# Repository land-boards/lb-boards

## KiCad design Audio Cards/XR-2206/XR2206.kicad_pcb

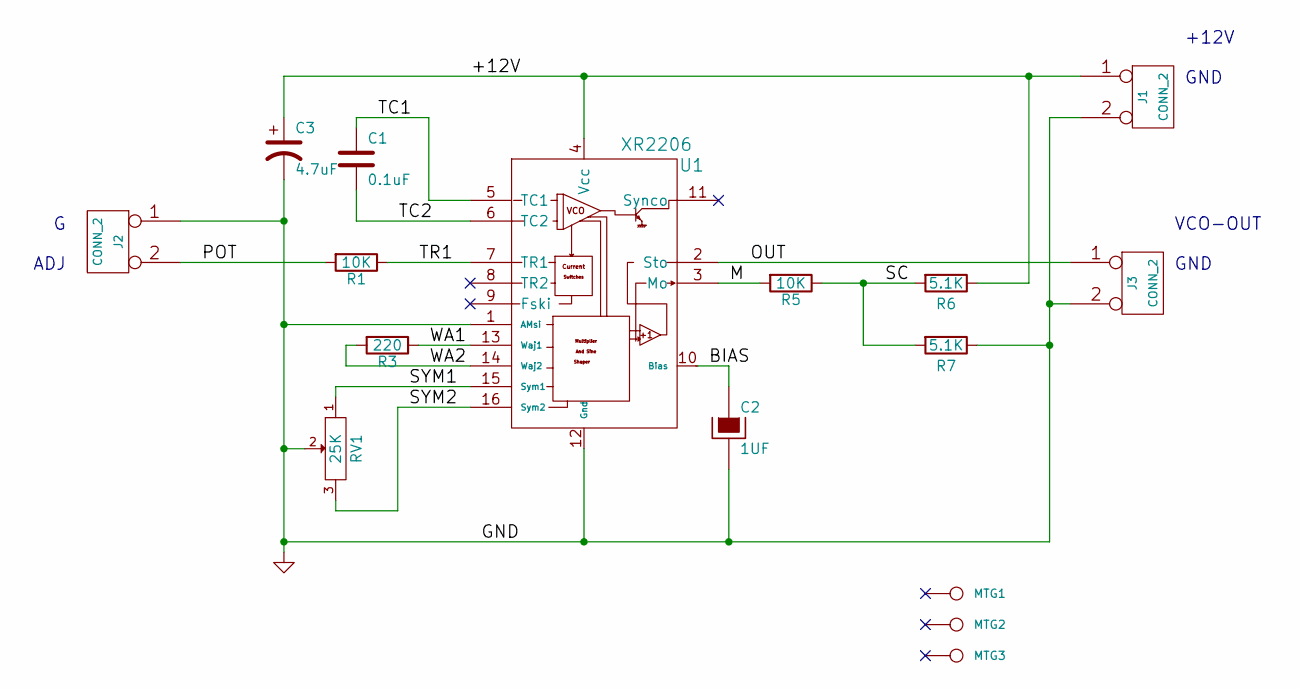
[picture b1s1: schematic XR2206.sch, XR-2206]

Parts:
C1: 0.1uF
C2: 1UF
C3: 4.7uF
J1, J2, J3: CONN_2
MTG1, MTG2, MTG3: CONN_1
R1, R5: 10K
R3: 220
R6, R7: 5.1K
RV1: 25K
U1: XR2206

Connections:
/+12V: C3.1, J1.1, R6.1, U1.4 (Vcc)
/BIAS: C2.1, U1.10 (Bias)
/M: R5.2, U1.3 (Mo)
/OUT: J3.1, U1.2 (Sto)
/POT: J2.2 (PM), R1.2
/SC: R5.1, R6.2, R7.2
/SYM1: RV1.1, U1.15 (Sym1)
/SYM2: RV1.3, U1.16 (Sym2)
/TC1: C1.1, U1.5 (TC1)
/TC2: C1.2, U1.6 (TC2)
/TR1: R1.1, U1.7 (TR1)
/WA1: R3.1, U1.13 (Waj1)
/WA2: R3.2, U1.14 (Waj2)
GND: C2.2, C3.2, J1.2 (PM), J2.1, J3.2 (PM), R7.1, RV1.2, U1.1 (AMsi), U1.12 (Gnd)

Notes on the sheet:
G ADJ
VCO-OUT GND
+12V GND

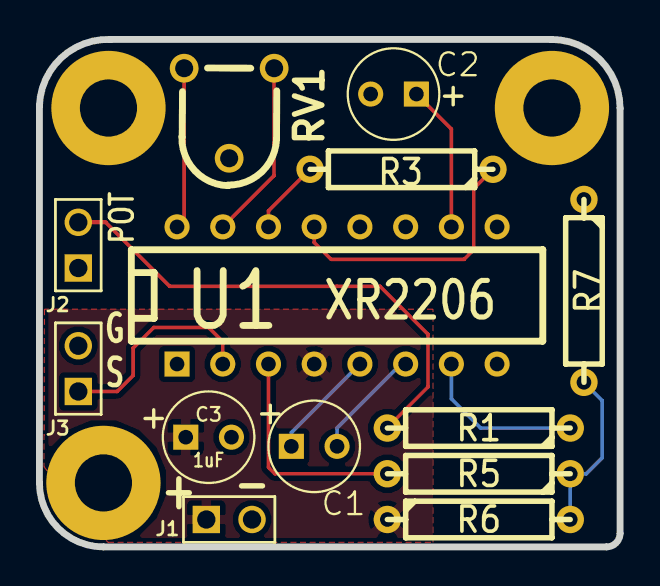
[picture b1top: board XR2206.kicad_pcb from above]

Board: 2 copper layers, 32.3 x 28.2 mm, 16 parts (0 on the bottom side), 14 nets.

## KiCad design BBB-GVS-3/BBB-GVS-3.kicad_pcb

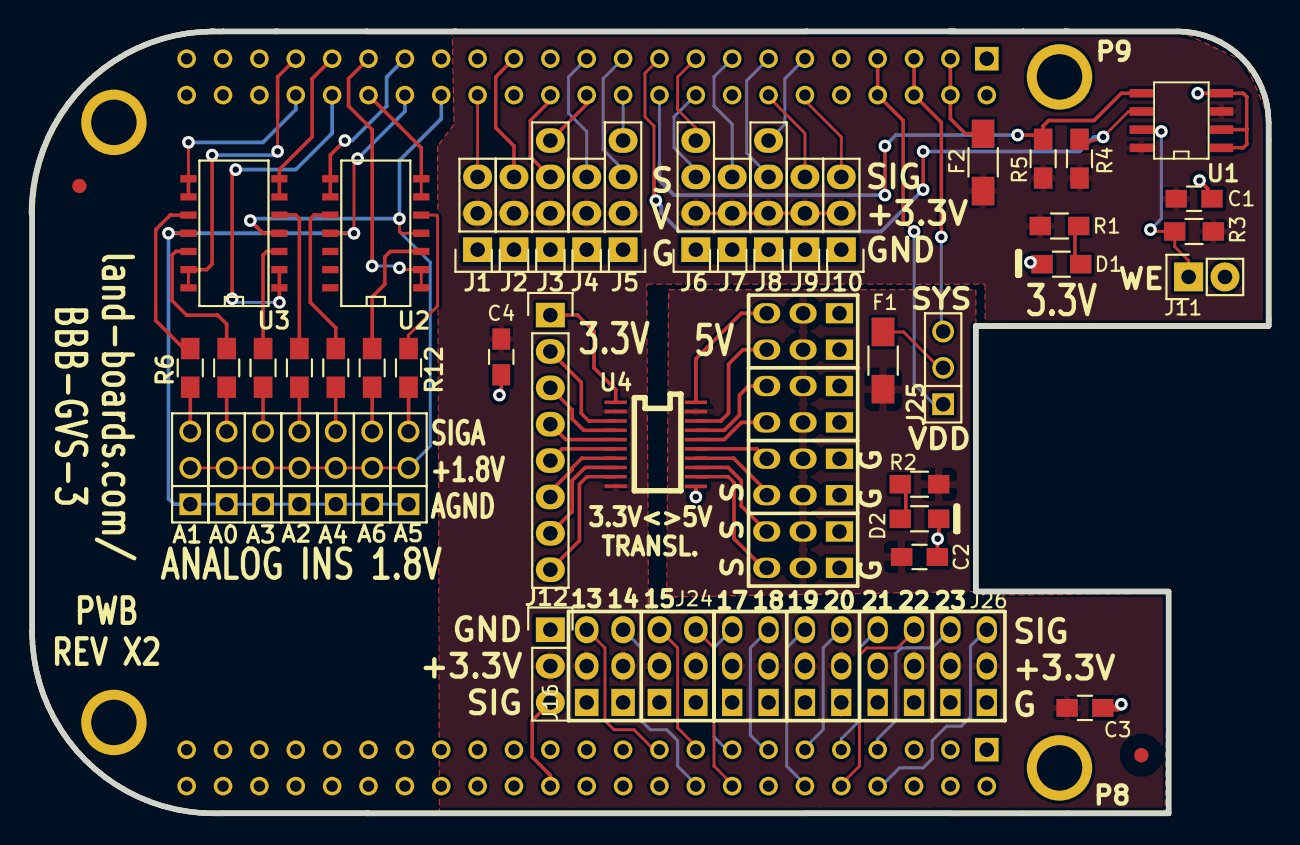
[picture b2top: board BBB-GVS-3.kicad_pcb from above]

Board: 2 copper layers, 86.4 x 54.6 mm, 53 parts (1 on the bottom side), 78 nets.

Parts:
A0, A1, A2, A3, A4, A5, A6: CONN_3; PIN_ARRAY_3X1
BRD1: BEAGLEBONE
C1: 1uF; C_0805_HandSoldering
C2, C3, C4: 104; C_0805_HandSoldering
D1, D2: LED; R_0805_HandSoldering
F1, F2: FUSE; C_1206_HandSoldering
FID1, FID2: CONN_1; FIDUCIAL
J1, J2, J4, J7, J9, J10, J12: CONN_3; Pin_Header_Straight_1x03
J3, J5, J6, J8: CONN_4; Pin_Header_Straight_1x04
J11: CONN_2; Pin_Header_Straight_1x02
J16: GVS-4X3; Pin_Header_Straight_3x04
J24, J26: GVS-8X3; Pin_Header_Straight_3x08
J25: CONN_3; PIN_ARRAY_3X1
P1: CONN_8; Pin_Header_Straight_1x08
R1: 120; R_0805_HandSoldering
R2: 330; R_0805_HandSoldering
R3, R4, R5: 5.6K; R_0805_HandSoldering
R6, R7, R8, R9, R10, R11, R12: 10K; R_0805_HandSoldering
TEST: COUPON; REV_BLOCK
TESTED1: COUPON; REV_BLOCK
U1: I2C-EEPROM; SO8E-wider
U2, U3: MCP6004-I/SL; SOIC-14_N
U4: TXS0108EPWR; SOG20

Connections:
/P8 Connector/EHRPWM2A: BRD1.B19, J16.3
/P8 Connector/EHRPWM2B: BRD1.B13, J24.6
/P8 Connector/GPIO0_27: BRD1.B17, J16.9
/P8 Connector/GPIO1_12: BRD1.B12, J24.9
/P8 Connector/GPIO1_13: BRD1.B11, J24.12
/P8 Connector/GPIO1_14: BRD1.B16, J16.12
/P8 Connector/GPIO1_15: BRD1.B15, J24.3
/P8 Connector/GPIO1_29: BRD1.B26, J12.3
/P8 Connector/GPIO2_1: BRD1.B18, J16.6
/P8 Connector/TIMER4: BRD1.B7, J24.21
/P8 Connector/TIMER5: BRD1.B9, J24.15
/P8 Connector/TIMER6: BRD1.B10, J24.18
/P8 Connector/TIMER7: BRD1.B8, J24.24
/P9 Connector/EHRPWM1A: BRD1.C14, J9.3
/P9 Connector/GPIO1_16: BRD1.C15, J7.3
/P9 Connector/GPIO1_17: BRD1.C23, J4.3
/P9 Connector/GPIO1_28: BRD1.C12, J10.3
/P9 Connector/GPIO3_19: BRD1.C27, J2.3
/P9 Connector/I2C1_SCL: BRD1.C17, J6.4
/P9 Connector/I2C1_SDA: BRD1.C18, J6.3
/P9 Connector/SPI1_D1: BRD1.C30, J1.3
/P9 Connector/UART1_RXD: BRD1.C26, J3.3
/P9 Connector/UART1_TXD: BRD1.C24, J3.4
/P9 Connector/UART2_RXD: BRD1.C22, J5.4
/P9 Connector/UART2_TXD: BRD1.C21, J5.3
/P9 Connector/UART4_RXD: BRD1.C11, J8.4
/P9 Connector/UART4_TXD: BRD1.C13, J8.3
AIN0: BRD1.C39, U3.13, U3.14
AIN1: BRD1.C40, U3.8, U3.9
AIN2: BRD1.C37, U3.6, U3.7
AIN3: BRD1.C38, U3.1, U3.2
AIN4: BRD1.C33, U2.8, U2.9
AIN5: BRD1.C36, U2.6, U2.7
AIN6: BRD1.C35, U2.1, U2.2
GND: BRD1.B1, BRD1.B2, BRD1.C1, BRD1.C2, BRD1.C43, BRD1.C44, BRD1.C45, BRD1.C46, C1.2, C2.2, C3.2, C4.2, D1.2, D2.2, J1.1, J2.1, J3.1, J4.1, J5.1, J6.1, J7.1, J8.1, J9.1, J10.1, J11.2, J12.1, J16.1, J16.4, J16.7, J16.10, J24.1, J24.4, J24.7, J24.10, J24.13, J24.16, J24.19, J24.22, J26.1, J26.4, J26.7, J26.10, J26.13, J26.16, J26.19, J26.22, U1.1, U1.2, U1.4, U4.11
GNDA_ADC: A0.1, A1.1, A2.1, A3.1, A4.1, A5.1, A6.1, BRD1.C34, U2.11, U3.11
I2C2_SCL: BRD1.C19, R4.2, U1.6
I2C2_SDA: BRD1.C20, R5.2, U1.5
unnamed: A0.3, R11.2
unnamed: A1.3, R9.2
unnamed: A2.3, R7.2
unnamed: A3.3, R12.2
unnamed: A4.3, R10.2
unnamed: A5.3, R8.2
unnamed: A6.3, R6.2
unnamed: D1.1, R1.2
unnamed: D2.1, R2.2
unnamed: F1.2, J25.2
unnamed: J11.1, R3.2, U1.7
unnamed: J26.3, U4.12
unnamed: J26.6, U4.13
unnamed: J26.9, U4.14
unnamed: J26.12, U4.15
unnamed: J26.15, U4.16
unnamed: J26.18, U4.17
unnamed: J26.21, U4.18
unnamed: J26.24, U4.20
unnamed: P1.1, U4.1
unnamed: P1.2, U4.3
unnamed: P1.3, U4.4
unnamed: P1.4, U4.5
unnamed: P1.5, U4.6
unnamed: P1.6, U4.7
unnamed: P1.7, U4.8
unnamed: P1.8, U4.9
unnamed: R6.1, U2.3
unnamed: R7.1, U3.5
unnamed: R8.1, U2.5
unnamed: R9.1, U3.10
unnamed: R10.1, U2.10
unnamed: R11.1, U3.12
unnamed: R12.1, U3.3
SYS_5V: BRD1.C7, BRD1.C8, J25.1
VDD_3V3-UF: BRD1.C3, BRD1.C4, F2.2
VDD_3V3EXP: C1.1, C3.1, C4.1, F2.1, J1.2, J2.2, J3.2, J4.2, J5.2, J6.2, J7.2, J8.2, J9.2, J10.2, J12.2, J16.2, J16.5, J16.8, J16.11, J24.2, J24.5, J24.8, J24.11, J24.14, J24.17, J24.20, J24.23, R1.1, R3.1, R4.1, R5.1, U1.3, U1.8, U4.2, U4.10
VDD_5V: C2.1, F1.1, J26.2, J26.5, J26.8, J26.11, J26.14, J26.17, J26.20, J26.23, R2.1, U4.19
VDD_5V-UF: BRD1.C5, BRD1.C6, J25.3
VDD_ADC: A0.2, A1.2, A2.2, A3.2, A4.2, A5.2, A6.2, BRD1.C32, U2.4, U3.4

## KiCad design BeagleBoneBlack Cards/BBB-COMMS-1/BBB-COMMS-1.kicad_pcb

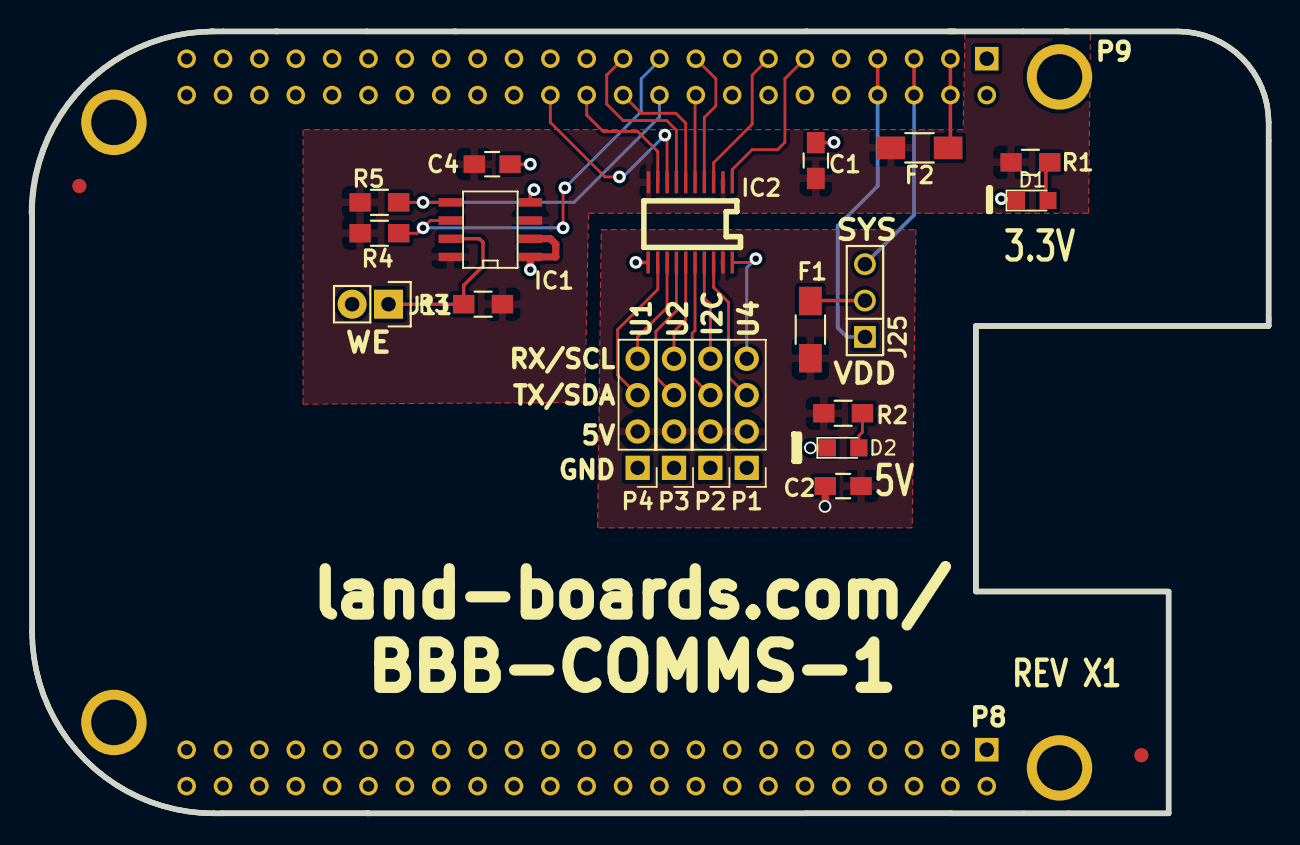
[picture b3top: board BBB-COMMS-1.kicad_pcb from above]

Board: 2 copper layers, 86.4 x 54.6 mm, 24 parts (0 on the bottom side), 28 nets.

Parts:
BRD1: BEAGLEBONE
C1: 1uF; C_0805_HandSoldering
C2, C4: 104; C_0805_HandSoldering
D1, D2: LED-fixed; LED_0805
F1, F2: FUSE; C_1206_HandSoldering
FID1, FID2: CONN_1; FIDUCIAL
IC1: I2C-EEPROM; SO8E-wider
IC2: TXB0108; SOG20
J11: CONN_2; Pin_Header_Straight_1x02
J25: CONN_3; PIN_ARRAY_3X1
P1, P2, P3, P4: CONN_01X04; Pin_Header_Straight_1x04_Pitch2.54mm
R1: 120; R_0805_HandSoldering
R2: 330; R_0805_HandSoldering
R3, R4, R5: 5.6K; R_0805_HandSoldering
TEST: COUPON; TEST_BLK-REAR

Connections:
/P9 Connector/I2C1_SCL: BRD1.C17, IC2.4
/P9 Connector/I2C1_SDA: BRD1.C18, IC2.5
/P9 Connector/SCL: IC2.17, P2.4
/P9 Connector/SDA: IC2.16, P2.3
/P9 Connector/U1RX: IC2.13, P4.4
/P9 Connector/U1TX: IC2.12, P4.3
/P9 Connector/U2RX: IC2.15, P3.4
/P9 Connector/U2TX: IC2.14, P3.3
/P9 Connector/U4RX: IC2.20, P1.4
/P9 Connector/U4TX: IC2.18, P1.3
/P9 Connector/UART1_RXD: BRD1.C26, IC2.8
/P9 Connector/UART1_TXD: BRD1.C24, IC2.9
/P9 Connector/UART2_RXD: BRD1.C22, IC2.6
/P9 Connector/UART2_TXD: BRD1.C21, IC2.7
/P9 Connector/UART4_RXD: BRD1.C11, IC2.1
/P9 Connector/UART4_TXD: BRD1.C13, IC2.3
GND: BRD1.B1, BRD1.B2, BRD1.C1, BRD1.C2, BRD1.C43, BRD1.C44, BRD1.C45, BRD1.C46, C1.2, C2.2, C4.2, D1.1, D2.1, IC1.1, IC1.2, IC1.4, IC2.11, J11.2, P1.1, P2.1, P3.1, P4.1
I2C2_SCL: BRD1.C19, IC1.6, R4.2
I2C2_SDA: BRD1.C20, IC1.5, R5.2
unnamed: D1.2, R1.2
unnamed: D2.2, R2.2
unnamed: F1.2, J25.2
unnamed: IC1.7, J11.1, R3.2
SYS_5V: BRD1.C7, BRD1.C8, J25.1
VCC_3V3EXP: C1.1, C4.1, F2.1, IC1.3, IC1.8, IC2.2, IC2.10, R1.1, R3.1, R4.1, R5.1
VDD_3V3-UF: BRD1.C3, BRD1.C4, F2.2
VDD_5V: C2.1, F1.1, IC2.19, P1.2, P2.2, P3.2, P4.2, R2.1
VDD_5V-UF: BRD1.C5, BRD1.C6, J25.3

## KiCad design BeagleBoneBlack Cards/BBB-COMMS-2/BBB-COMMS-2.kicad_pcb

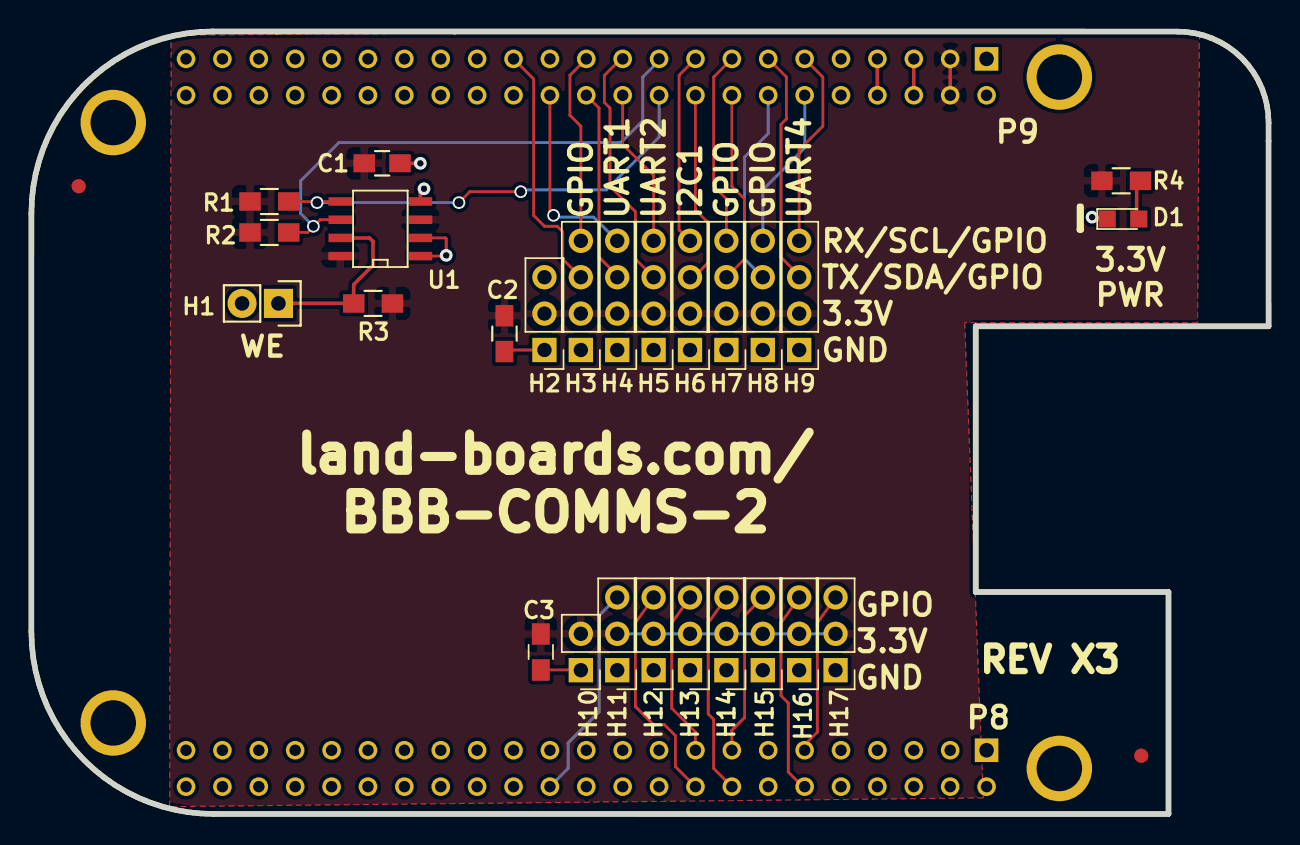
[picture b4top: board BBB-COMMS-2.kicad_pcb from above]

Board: 2 copper layers, 86.4 x 54.6 mm, 30 parts (0 on the bottom side), 29 nets.

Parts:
BRD1: BEAGLEBONE
C1, C3: 104; C_0805_HandSoldering
C2: 1uF; C_0805_HandSoldering
D1: LED-fixed; LED_0805
FID1, FID2: CONN_1; FIDUCIAL
H1: CONN_2; Pin_Header_Straight_1x02
H2, H11, H12, H13, H14, H15, H16, H17: CONN_01X03; Pin_Header_Straight_1x03_Pitch2.54mm
H3, H4, H5, H6, H7, H8, H9: CONN_01X04; Pin_Header_Straight_1x04_Pitch2.54mm
H10: CONN_01X02; Pin_Header_Straight_1x02_Pitch2.54mm
R1, R2, R3: 5.6K; R_0805_HandSoldering
R4: 120; R_0805_HandSoldering
TEST: COUPON; TEST_BLK-REAR
U1: I2C-EEPROM; SO8E-wider

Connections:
/P8 Connector/GPIO0_27: BRD1.B17, H13.3
/P8 Connector/GPIO1_12: BRD1.B12, H16.3
/P8 Connector/GPIO1_13: BRD1.B11, H17.3
/P8 Connector/GPIO1_14: BRD1.B16, H14.3
/P8 Connector/GPIO1_15: BRD1.B15, H15.3
/P8 Connector/GPIO1_29: BRD1.B26, H11.3
/P8 Connector/GPIO2_1: BRD1.B18, H12.3
/P9 Connector/EHRPWM1A: BRD1.C14, H8.3
/P9 Connector/EHRPWM1B: BRD1.C16, H7.3
/P9 Connector/GPIO1_16: BRD1.C15, H7.4
/P9 Connector/GPIO1_17: BRD1.C23, H3.4
/P9 Connector/GPIO1_28: BRD1.C12, H8.4
/P9 Connector/GPIO3_19: BRD1.C27, H3.3
/P9 Connector/I2C1_SCL: BRD1.C17, H6.4
/P9 Connector/I2C1_SDA: BRD1.C18, H6.3
/P9 Connector/UART1_RXD: BRD1.C26, H4.4
/P9 Connector/UART1_TXD: BRD1.C24, H4.3
/P9 Connector/UART2_RXD: BRD1.C22, H5.4
/P9 Connector/UART2_TXD: BRD1.C21, H5.3
/P9 Connector/UART4_RXD: BRD1.C11, H9.4
/P9 Connector/UART4_TXD: BRD1.C13, H9.3
GND: BRD1.B1, BRD1.B2, BRD1.C1, BRD1.C2, BRD1.C43, BRD1.C44, BRD1.C45, BRD1.C46, C1.2, C2.2, C3.2, D1.1, H1.2, H2.1, H3.1, H4.1, H5.1, H6.1, H7.1, H8.1, H9.1, H10.1, H11.1, H12.1, H13.1, H14.1, H15.1, H16.1, H17.1, U1.1, U1.2, U1.4
I2C2_SCL: BRD1.C19, R2.2, U1.6
I2C2_SDA: BRD1.C20, R1.2, U1.5
unnamed: D1.2, R4.2
unnamed: H1.1, R3.2, U1.7
SYS_5V: BRD1.C7, BRD1.C8
VDD_3V3-UF: BRD1.C3, BRD1.C4, C1.1, C2.1, C3.1, H2.2, H3.2, H4.2, H5.2, H6.2, H7.2, H8.2, H9.2, H10.2, H11.2, H12.2, H13.2, H14.2, H15.2, H16.2, H17.2, R1.1, R2.1, R3.1, R4.1, U1.3, U1.8
VDD_5V-UF: BRD1.C5, BRD1.C6
